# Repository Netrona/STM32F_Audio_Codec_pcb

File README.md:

# STM32F+Audio Codec PCB Design Project

## Description 

This project is designed to interface STM32F405 with the audio codec WM8731. The board supports the development of audio applications. 

### STM32F4 Pinout selection 

I used STM32CubeMX software to configure STM32F405RGT6 MCU chip. The used connections are:

• USART2

• I2S2

• I2C1

• USB_FS 

## Schematic Design

## PCB Design

### Full tracks overveiw 

### Tracks with filled zones overveiw 

### 3D overview 

#### Top veiw 

#### Bottom veiw

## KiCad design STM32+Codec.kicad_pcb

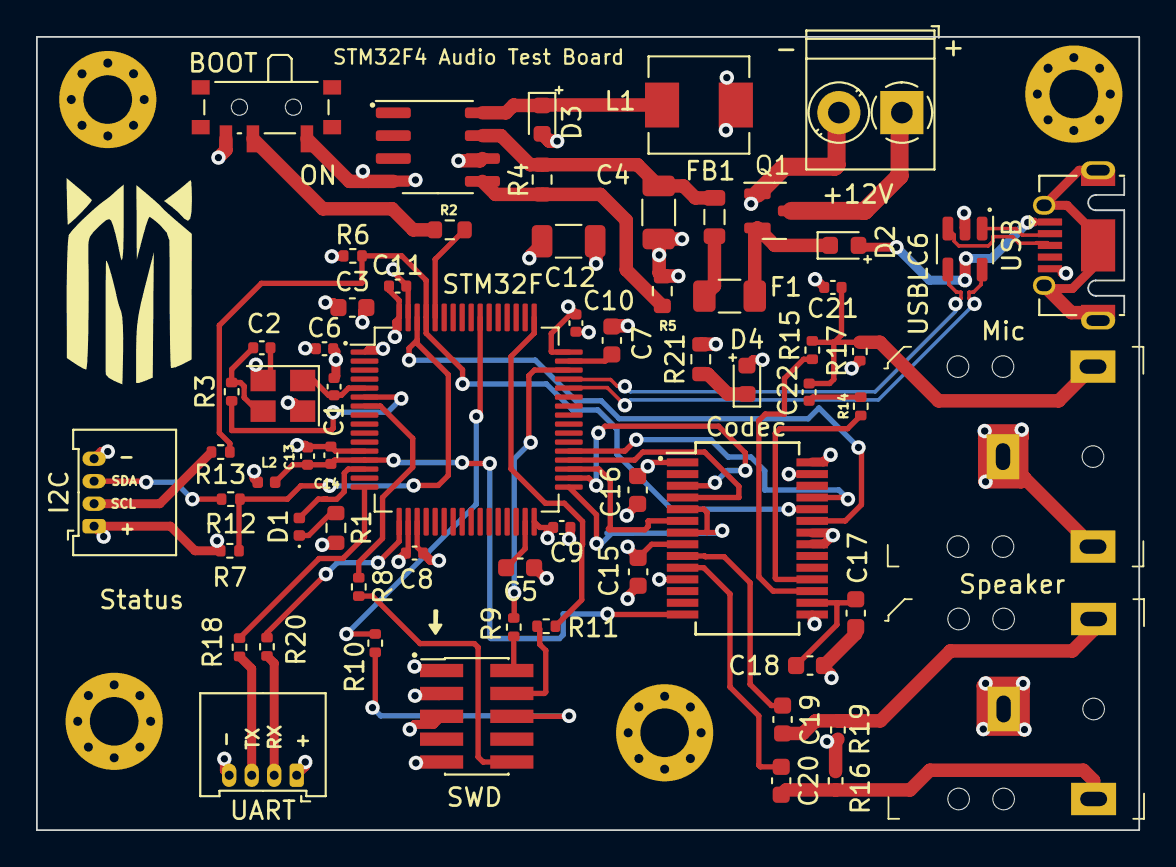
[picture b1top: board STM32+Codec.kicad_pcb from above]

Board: 4 copper layers, 61.2 x 44.1 mm, 69 parts (0 on the bottom side), 54 nets.

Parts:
+12V: Power; TerminalBlock_Phoenix_PT-1,5-2-3.5-H_1x02_P3.50mm_Horizontal
BOOT: SW_SPDT; SW_SPDT_PCM12
C1, C2: 12p; C_0402_1005Metric
C3: 4u7; C_0603_1608Metric
C4: 68u; C_1206_3216Metric
C5, C7: 2u2; C_0603_1608Metric
C6, C8, C9, C10, C11: 100n; C_0402_1005Metric
C12: 120u; C_1206_3216Metric
C13: 1u; C_0402_1005Metric
C14: 10n; C_0402_1005Metric
C15, C16, C18: 0.1u; C_0603_1608Metric
C17: 10u; C_0603_1608Metric
C19, C20: 330u; C_0603_1608Metric
C21, C22: 1n; C_0402_1005Metric
Codec: WM8731SEDS; SSOP-28_5.3x10.2mm_P0.65mm
D1: LED; LED_0402_1005Metric
D2, D3: 1N5817; D_0603_1608Metric
D4: LED; LED_0603_1608Metric
F1: 250mA; Fuse_1206_3216Metric
FB1: 600 @ 600MHz; L_0805_2012Metric
H1, H2, H3, H4: MH; MountingHole_2.7mm_Pad_Via
I2C: Conn_01x04; Molex_PicoBlade_53048-0410_1x04_P1.25mm_Horizontal
L1: 47u; L_Sunlord_MWSA0518_5.4x5.2mm
L2: 39n; L_0402_1005Metric
Mic: SJ1-3523N; Headphone_Jack_3.5mm_SJ1-3523N
Q1: AO3401A; SOT-23
R1, R21: 1k5; R_0603_1608Metric
R2: 10K; R_0603_1608Metric
R3: 45; R_0402_1005Metric
R4: 100k; R_0603_1608Metric
R5: 68k; R_0603_1608Metric
R6, R7: 2.2k; R_0402_1005Metric
R8, R9, R10, R11, R12, R13, R18, R20: 22; R_0402_1005Metric
R14: 330; R_0402_1005Metric
R15: 680; R_0402_1005Metric
R16, R17, R19: 47k; R_0402_1005Metric
STM32F: STM32F405RGTx; LQFP-64_10x10mm_P0.5mm
SWD: SWD; PinHeader_2x05_P1.27mm_Vertical_SMD
Speaker: SJ1-3523N; Headphone_Jack_3.5mm_SJ1-3523N
U2: LM2594HVM-3.3; SOIC-8_3.9x4.9mm_P1.27mm
UART: Conn_01x04; Molex_PicoBlade_53048-0410_1x04_P1.25mm_Horizontal
USB: USB_B_Mini; USB_Micro-AB_Molex_47590-0001
USBLC6: USBLC6-2SC6; SOT-23-6
Y1: 16MHz; Crystal_SMD_3225-4Pin_3.2x2.5mm

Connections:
+3.3VA: C13.1, C14.1, Codec.14 (AVDD), L2.2, STM32F.13 (VDDA)
+5V: D2.2 (A), USB.1 (VBUS), USBLC6.5 (VBUS)
+12V: +12V.1, Q1.3 (D)
BOOT0: R2.2, STM32F.60 (BOOT0)
DBVDD: BOOT.1 (A), C3.1, C6.1, C8.1, C9.1, C10.1, C11.1, C12.1, C15.1, C16.1, Codec.1 (DBVDD), Codec.8 (HPVDD), Codec.27 (DCVDD), D4.2 (A), I2C.1, L1.2, L2.1, R6.1, R7.1, STM32F.1 (VBAT), STM32F.19 (VDD), STM32F.32 (VDD), STM32F.48 (VDD), STM32F.64 (VDD), SWD.1, U2.4 (FB), UART.1
GND: +12V.2, BOOT.3 (C), C1.2, C2.2, C3.2, C4.2, C5.2, C6.2, C7.2, C8.2, C9.2, C10.2, C11.2, C12.2, C13.2, C14.2, C15.2, C16.2, C17.2, C18.2, C21.2, Codec.11 (HPGND), Codec.15 (AGND), Codec.21 (MODE), Codec.22 (~CSB), Codec.28 (DGND), D3.2 (A), H1.1, H2.1, H3.1, H4.1, I2C.4, Mic.1 (S), Mic.2 (T), Q1.1 (G), R1.2, R5.2, R16.2, R17.2, R19.2, R21.2, STM32F.12 (VSSA), STM32F.18 (VSS), STM32F.63 (VSS), SWD.3, SWD.5, SWD.9, Speaker.1 (S), U2.6 (GND), UART.4, USB.5 (GND), USBLC6.2 (GND), Y1.2, Y1.4
HSE_IN: C1.1, STM32F.5 (PH0), Y1.1
HSE_OUT: R3.2, STM32F.6 (PH1)
I2C_SCL: Codec.24 (SCLK), R6.2, R13.1, STM32F.61 (PB8)
I2C_SDA: Codec.23 (SDIN), R7.2, R12.1, STM32F.62 (PB9)
I2S_LRCK: Codec.5 (DACLRC), Codec.7 (ADCLRC), STM32F.33 (PB12)
I2S_MCLK: Codec.25 (XTI/MCLK), STM32F.37 (PC6)
I2S_SCLK: Codec.3 (BCLK), STM32F.34 (PB13)
I2S_SDI: Codec.6 (ADCDAT), STM32F.35 (PB14)
I2S_SDO: Codec.4 (DACDAT), STM32F.36 (PB15)
LED_STATUS: D1.2 (A), STM32F.14 (PA0)
LHPO: C19.1, Codec.9 (LHPOUT)
MICBIAS: Codec.17 (MICBIAS), R15.1
MICIN: Codec.18 (MICIN), R14.1
NRST: R8.1, STM32F.7 (NRST)
unnamed: C2.1, R3.1, Y1.3
unnamed: C4.1, FB1.2, R4.1, U2.7 (VIN)
unnamed: C5.1, STM32F.31 (VCAP_1)
unnamed: C7.1, STM32F.47 (VCAP_2)
unnamed: C17.1, C18.1, Codec.16 (VMID)
unnamed: C19.2, R19.1, Speaker.3 (R)
unnamed: C20.2, R16.1, Speaker.2 (T)
unnamed: C21.1, C22.2, Mic.3 (R), R15.2, R17.1
unnamed: C22.1, R14.2
unnamed: D1.1 (K), R1.1
unnamed: D2.1 (K), F1.1, Q1.2 (S)
unnamed: D4.1 (K), R21.1
unnamed: F1.2, FB1.1
unnamed: R9.1, SWD.2
unnamed: R11.2, SWD.4
unnamed: R10.2, SWD.6
unnamed: R8.2, SWD.10
unnamed: I2C.2, R13.2
unnamed: I2C.3, R12.2
unnamed: R20.2, UART.2
unnamed: R18.2, UART.3
unnamed: D3.1 (K), L1.1, U2.8 (OUT)
unnamed: BOOT.2 (B), R2.1
unnamed: R4.2, R5.1, U2.5 (~ON/OFF)
RHPO: C20.1, Codec.10 (RHPOUT)
RXD: R20.1, STM32F.17 (PA3)
SWCLK: R11.1, STM32F.49 (PA14)
SWDIO: R9.2, STM32F.46 (PA13)
SWO: R10.1, STM32F.55 (PB3)
TXD: R18.1, STM32F.16 (PA2)
USB_CONN_D+: USB.3 (D+), USBLC6.3 (I/O2)
USB_CONN_D-: USB.2 (D-), USBLC6.1 (I/O1)
USB_D+: STM32F.45 (PA12), USBLC6.4 (I/O2)
USB_D-: STM32F.44 (PA11), USBLC6.6 (I/O1)
